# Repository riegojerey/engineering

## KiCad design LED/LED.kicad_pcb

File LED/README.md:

# LED indicator — 9 V, single LED

Status: **schematic and PCB complete, ERC and DRC clean.** Not yet sourced
(fixes 6–9 below) and not yet fabbed.

## Design

Chain: `BT1+ → R1 → D2 (A→K) → D1 (A→K) → GND (BT1−)`

| Ref | Part | Value | Footprint |
|-----|------|-------|-----------|
| BT1 | 9 V PP3 battery holder | `9V` | `Battery:BatteryHolder_MPD_BA9VPC_1xPP3` |
| R1  | current-limiting resistor | `620` | `Resistor_SMD:R_0805_2012Metric` |
| D2  | series reverse-polarity protection | `1N4148W` | `Diode_SMD:D_SOD-123` |
| D1  | indicator LED | `LED` | `LED_SMD:LED_0805_2012Metric` |

`R1 = (Vbat − Vf_LED − Vf_D2) / I = (9 − 2.0 − 0.7) / 620 ≈ 10.2 mA`, and the
SPICE `.op` run gives **10.14 mA** with **64 mW** in R1. Vf is assumed for a red
LED; a blue/white part (Vf 3.2) gives 8.2 mA at 620 Ω, or use 510 Ω for 10 mA.
**Do not fit 47 Ω**: with D2 forward that is 133 mA and 828 mW in R1.

D2 is deliberate, not leftover. It blocks a reversed battery instead of
destroying the LED, and a series diode is the right choice for an unfused
battery loop (a shunt diode would dead-short the pack). It costs 0.7 V by
design and R1 is sized with that drop included. Neither D2 nor D1 may be
flipped: a reversed D2 makes the circuit an open circuit.

## Board

66 × 44 mm, 2 layers, ground pour on B.Cu, one via. The size is set by the PP3
holder (56 × 33 mm), not by the circuit.

Routing: chain parts in a row at y = 38 mm; `Net-(BT1-+)` runs down the left
board margin (x = 1.8 mm) to stay clear of the holder; D1's cathode reaches the
B.Cu pour through one via at (33, 38).

One deliberate trade-off: ~2.5 mm of the `Net-(BT1-+)` segment leaves pad 1 at
y = 11 mm inside the holder's outline. The holder lifts the cell off the board
and that area is covered by holder plastic, so it is electrically safe. If you
want literally zero copper under the holder, run that segment on B.Cu instead —
pad 1 is THT so it already exists there — and bring it back up with a via next
to R1 pad 1.

## Verification

| Check | Command | Result |
|-------|---------|--------|
| ERC | `kicad-cli sch erc LED.kicad_sch` | 0 errors (7 warnings, all environmental `lib_symbol_issues` — this box has no `sym-lib-table`, the symbols are embedded in the sheet) |
| DRC | `kicad-cli pcb drc --schematic-parity --severity-all LED.kicad_pcb` | **0 violations, 0 unconnected, 0 parity issues** |
| DRC rules live | mutated copy with a 0.10 mm track | correctly flagged `track_width` + `clearance` |
| Netlist parity | `kicad-cli sch export netlist` + `--schematic-parity` | board matches schematic exactly |
| Current | `ngspice -b` on the equivalent netlist | 10.14 mA, 64 mW in R1 |

DRC rules in `LED.kicad_pro` are set to a JLCPCB-comfortable floor:
min track 0.2 mm, min clearance 0.2 mm, min via 0.6/0.3 mm, copper-to-edge 0.5 mm.
The project shipped with `min_clearance: 0.0` and `min_track_width: 0.0`, which
made a passing DRC meaningless.

## 2026-09-20 review fixes applied (items 1–5)

1. **One canonical design.** The broken original is quarantined as
   `archive/LED-original-broken.*` (D2 reversed → open circuit, 47 Ω resistor,
   `10V` on a 1.5 V cell symbol, no footprints). `LED.*` is now the corrected
   design, formerly named `LED-revised`.
2. **D2 kept at 90°** (forward) and documented on the sheet with a text note
   explaining its purpose and that its polarity is load-bearing.
3. **R1 kept at 620 Ω** and documented on the sheet with the sizing formula.
4. **Battery fixed**: `Device:Battery_Cell` (a 1.5 V cell) replaced with
   `Device:Battery` (multi-cell), value `9V`, with a real PP3 holder footprint.
   The GND symbol and PWR_FLAG moved to the new pin-2 position, so the netlist
   is unchanged from the corrected revision.
5. **Board built, routed, DRC'd** — from an empty 78-byte stub to a real
   2-layer board, with footprints on all four parts.

## Open items

- **Fix 6 — sourcing/MPN (`SS-001`, `DS-001`)**: still 0/4 BOM lines have an
  MPN and there is no `datasheets/` directory. Run the `digikey`/`lcsc` skills
  and write MPNs into the symbol properties.
- **Fix 3 follow-up**: revisit R1 if the LED colour changes from red.
- **Fix 8 — title block** is still empty in the schematic (no title/rev/date).
- **Fix 9 — backup housekeeping**: `LED-backups/LED-2026-09-20_092742.zip`
  contains a stale `~LED.kicad_sch.lck` and a third schematic variant (20,572 B)
  matching neither file on disk.
- **Fabrication outputs** (gerbers, drill, CPL) have not been generated.
- **Fiducials / test points**: `FD-001` and `TE-001` flag these. Only needed if
  you machine-assemble or test this board at volume; hand assembly doesn't need
  them.
- **`LR-001` is a false positive and will keep appearing.** The analyzer reports
  "LED D1: no current-limiting resistor found" on this design. R1 *is* in series
  (battery+ → R1 → D2 → D1 → GND, confirmed by netlist). The detector
  (`skills/kicad/scripts/validation_detectors.py`, `validate_led_resistors`) only
  recognises a resistor that shares a net directly with the LED *and* whose other
  terminal is on a net whose name parses as a power/ground rail. D2 breaks the
  adjacency and the battery net is unnamed (`Net-(BT1-+)`), so it falls into the
  "no resistor at all" branch — while the branch that would catch a genuine
  overcurrent never runs. No detector in the pack evaluates diode orientation or
  DC path continuity, which is why the reversed-D2 original and the working board
  produced identical finding sets.

## KiCad traps hit while doing this

- **Two `.kicad_pro` files in one directory silently redirect analysis.** Name a
  file and the analyzer resolves the project root instead, describing a
  different board with full confidence. Never keep two projects in one folder.
- **`ZONE_FILLER.Fill()` segfaults on a `CreateEmptyBoard()` board** but works on
  a board loaded back from disk. Build → save → reload → fill → save.
- **`PCB_VIA.SetWidth()` in KiCad 9 takes an explicit layer.** A bare call trips a
  C++ assert and kills the process before anything is written.
- **`FootprintLoad()` sets only the item name**, so the library nickname has to be
  restored with `SetFPID()` or `DRC --schematic-parity` reports a
  `footprint_symbol_mismatch` on every part.
- **Writing a board whose project pcbnew does not hold rewrites the sibling
  `.kicad_pro` with in-memory defaults**, resetting the design rules to
  `min_clearance: 0.0` / `min_track_width: 0.0`. Apply rule changes *after* any
  board build, and read them back.

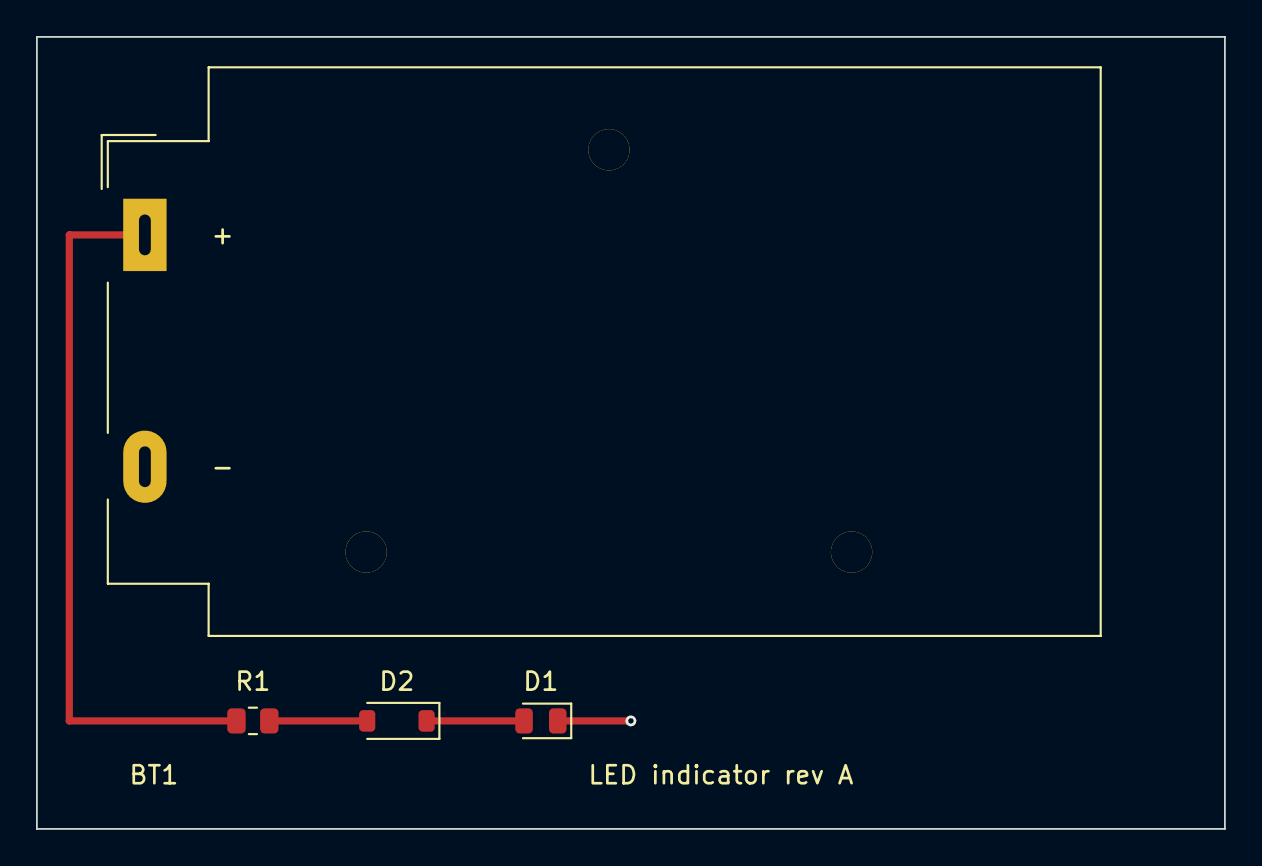
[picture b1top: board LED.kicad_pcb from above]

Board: 2 copper layers, 66.0 x 44.0 mm, 4 parts (0 on the bottom side), 4 nets.

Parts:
BT1: 9V; BatteryHolder_MPD_BA9VPC_1xPP3
D1: LED; LED_0805_2012Metric
D2: 1N4148W; D_SOD-123
R1: 620; R_0805_2012Metric

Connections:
GND: BT1.2, D1.1
unnamed: BT1.1, R1.1
unnamed: D1.2, D2.1
unnamed: D2.2, R1.2

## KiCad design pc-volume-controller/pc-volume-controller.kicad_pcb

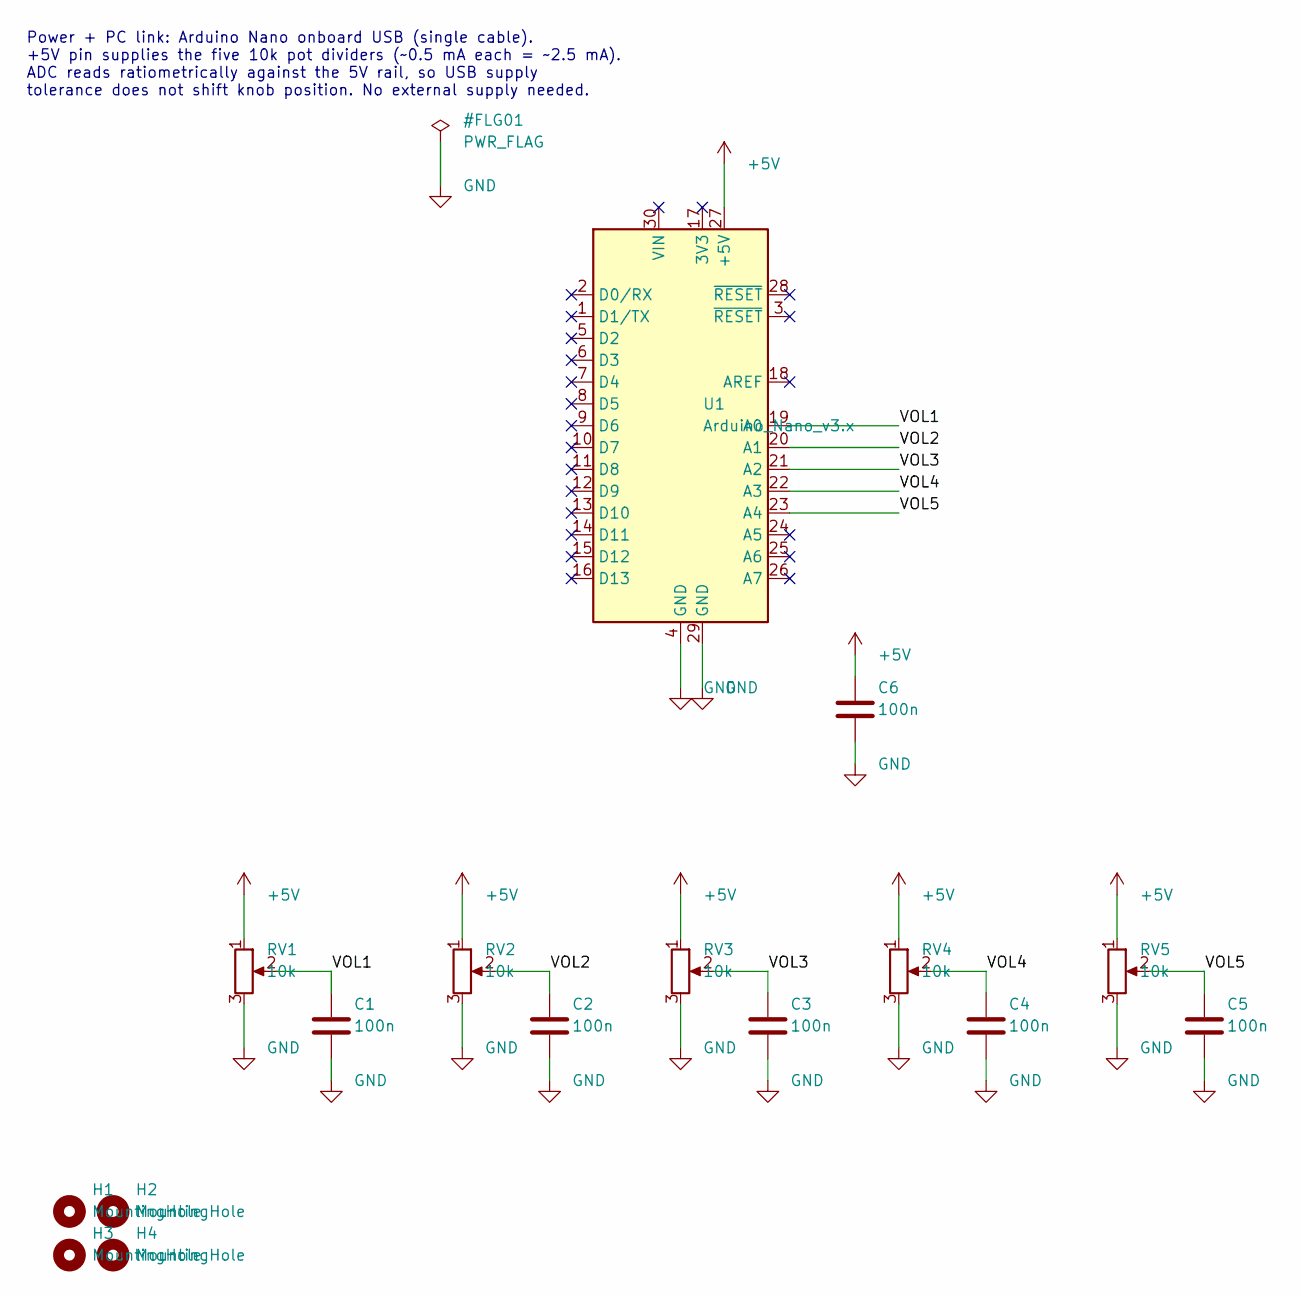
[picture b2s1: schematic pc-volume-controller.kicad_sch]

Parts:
C1, C2, C3, C4, C5, C6: 100n; C_0805_2012Metric
H1, H2, H3, H4: MountingHole; MountingHole_3.2mm_M3
RV1, RV2, RV3, RV4, RV5: 10k; Potentiometer_Alpha_RD901F-40-00D_Single_Vertical
U1: Arduino_Nano_v3.x; Arduino_Nano

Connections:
+5V: C6.1, RV1.1, RV2.1, RV3.1, RV4.1, RV5.1, U1.27 (+5V)
/VOL1: C1.1, RV1.2, U1.19 (A0)
/VOL2: C2.1, RV2.2, U1.20 (A1)
/VOL3: C3.1, RV3.2, U1.21 (A2)
/VOL4: C4.1, RV4.2, U1.22 (A3)
/VOL5: C5.1, RV5.2, U1.23 (A4)
GND: C1.2, C2.2, C3.2, C4.2, C5.2, C6.2, RV1.3, RV2.3, RV3.3, RV4.3, RV5.3, U1.4 (GND), U1.29 (GND)

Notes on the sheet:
Power + PC link: Arduino Nano onboard USB (single cable). +5V pin supplies the five 10k pot dividers (~0.5 mA each = ~2.5 mA). ADC reads ratiometrically against the 5V rail, so USB supply tolerance does not shift knob position. No external supply needed.

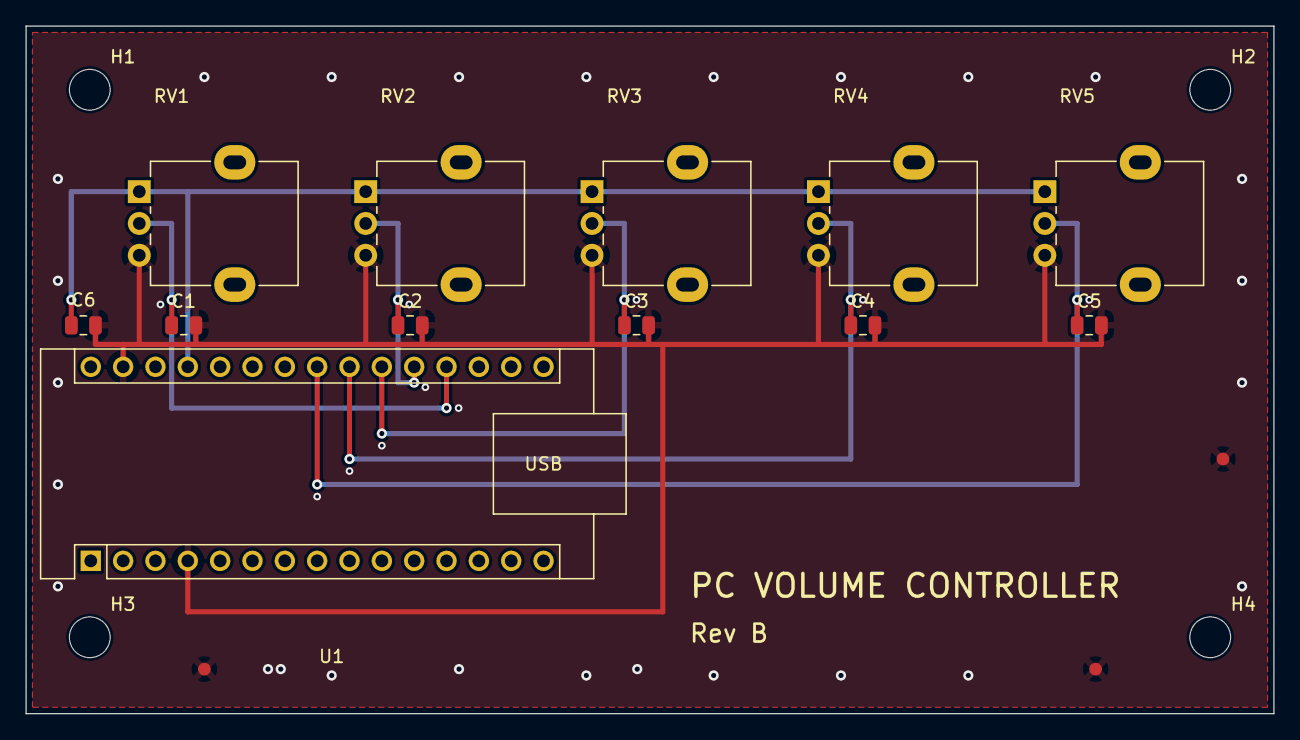
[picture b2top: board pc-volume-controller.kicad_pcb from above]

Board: 2 copper layers, 98.0 x 54.0 mm, 19 parts (0 on the bottom side), 7 nets.

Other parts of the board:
FID1, FID2, FID3: Fiducial_1mm_Mask2mm

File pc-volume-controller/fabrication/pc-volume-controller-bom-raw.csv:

"Refs","Value","Footprint","Qty","DNP"
"C1","100n","Capacitor_SMD:C_0805_2012Metric","1",""
"C2","100n","Capacitor_SMD:C_0805_2012Metric","1",""
"C3","100n","Capacitor_SMD:C_0805_2012Metric","1",""
"C4","100n","Capacitor_SMD:C_0805_2012Metric","1",""
"C5","100n","Capacitor_SMD:C_0805_2012Metric","1",""
"C6","100n","Capacitor_SMD:C_0805_2012Metric","1",""
"H1","MountingHole","MountingHole:MountingHole_3.2mm_M3","1",""
"H2","MountingHole","MountingHole:MountingHole_3.2mm_M3","1",""
"H3","MountingHole","MountingHole:MountingHole_3.2mm_M3","1",""
"H4","MountingHole","MountingHole:MountingHole_3.2mm_M3","1",""
"RV1","10k","Potentiometer_THT:Potentiometer_Alpha_RD901F-40-00D_Single_Vertical","1",""
"RV2","10k","Potentiometer_THT:Potentiometer_Alpha_RD901F-40-00D_Single_Vertical","1",""
"RV3","10k","Potentiometer_THT:Potentiometer_Alpha_RD901F-40-00D_Single_Vertical","1",""
"RV4","10k","Potentiometer_THT:Potentiometer_Alpha_RD901F-40-00D_Single_Vertical","1",""
"RV5","10k","Potentiometer_THT:Potentiometer_Alpha_RD901F-40-00D_Single_Vertical","1",""
"U1","Arduino_Nano_v3.x","Module:Arduino_Nano","1",""
